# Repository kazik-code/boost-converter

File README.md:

# Przetwornica Boost — README

Autorski projekt przetwornicy podwyższającej napięcie (DC-DC step-up) z regulacją napięcia wyjściowego (CV) i ograniczeniem prądowym (CC). Projekt obejmuje pełny cykl inżynierski: schemat → symulacja LTSpice → projekt PCB (KiCad) → montaż → pomiary i weryfikacja na sprzęcie.

**Projekt grupowy:** 3×Kuba, 1×Szymon

---

## Kluczowe Parametry

| Parametr | Wartość spec. |
| --- | --- |
| Częstotliwość kluczowania | ~1,6 MHz |
| Indukcyjność cewki | L1 = 40 µH |
| Pojemność wyjściowa (bulk) | C2 = 200 µF |
| Próg ograniczenia prądu (CC) | ~300 mA |
| Napięcie wyjściowe (CV) | regulowane przez RV1 |
| Napięcie wejściowe | [Vin] V |

---

## Schemat Blokowy

## Architektura Układu

### 1. Stopień Boost — LM27313XMF + L1 + D1

**LM27313XMF** to kontroler PWM przetwornicy boost o stałej częstotliwości (~1,6 MHz). Reguluje napięcie wyjściowe porównując napięcie na pinie FB z wewnętrznym napięciem referencyjnym — wyższe napięcie FB oznacza większy współczynnik wypełnienia.

Gdy wewnętrzny przełącznik (SW) zamknięty, zwiera dolny koniec cewki **L1 (40 µH)** do masy — prąd narasta, gromadząc energię w polu magnetycznym. Gdy SW otwiera się, pole opada i cewka działa jako źródło prądu napędzające wyjście do napięcia wyższego niż wejście.

**D1 (1N5822 Schottky)** — dioda swobodnego biegu. Gdy SW otwiera się, zapewnia jedyną ścieżkę przepływu prądu cewki. Bez niej zanikające pole wytworzyłoby skok napięcia niszczący U1. Schottky wybrano ze względu na niski spadek napięcia (~0,35 V vs ~0,7 V dla krzemu) i zerowy czas rekombinacji nośników odwrotnych — kluczowe przy 1,574 MHz.

**RV1 (potencjometr 100 kΩ)** ustawia napięcie na pinie FB, regulując tym samym napięcie wyjściowe. **C3 (2,2 µF)** blokuje zakłócenia HF na zasilaniu LM27313.

### 2. Filtr Wyjściowy

| Element | Wartość | Rola |
| --- | --- | --- |
| C1 | 200 pF | Ceramiczny bypass HF — tłumi szumy kluczowania |
| C2 | 200 µF | Elektrolityczny bulk — główny rezerwuar energii, stabilizuje wyjście między cyklami |
| C4 | 10 pF | Drugi bypass HF, blisko wejścia LM317 |

### 3. Pomiar Prądu Cewki — R2 + U2A

**R2 (1 Ω)** w szeregu z torem mocy (bypassowalny przez SW2). Wzmacniacz różnicowy **U2A** (LM358, R3=R4=R5=R6=9,53 kΩ, wzmocnienie = 1) mierzy spadek napięcia:

```
V_out(U2A) = I_cewki × 1 Ω
```

Wynik dostępny na **J3** do zewnętrznego pomiaru. SW2 pozwala ominąć R2 eliminując straty I²R gdy monitoring nie jest potrzebny.

### 4. Regulacja CV/CC — LM317 + U2B + Q1

**LM317 (U3)** jako liniowy regulator po stopniu boost, utrzymuje 1,25 V między OUT i ADJ. **R7** ustawia bazowe napięcie wyjściowe.

**R8 ‖ R9 = 0,5 Ω** mierzą prąd wyjściowy. **U2B** (LM358, wzmacniacz nieodwracający) wzmacnia sygnał:

```
Wzmocnienie = 1 + R11/R10 = 1 + 24k/3,3k ≈ 8,27

Przy I_out = 300 mA:
  V_sense = 0,300 × 0,5  = 0,150 V
  V_U2B   = 0,150 × 8,27 ≈ 1,24 V  ≈  V_ref(LM317) = 1,25 V
```

Gdy V_U2B ≈ 1,25 V, **Q1 (NPN)** przewodzi i ściąga pin ADJ do masy — LM317 obniża napięcie wyjściowe utrzymując I_out ≈ 300 mA (tryb CC). Poniżej progu Q1 zatkany, LM317 reguluje normalnie (tryb CV). Elegancja projektu: próg CC jest wyznaczony przez napięcie referencyjne samego LM317 — bez osobnego komparatora.

---

## Schemat i PCB

### Schemat (KiCad)

### Render 3D PCB

### Zmontowana płytka

Płytka dwuwarstwowa z wyraźną separacją torów mocy i sygnałowych. Toroidalny rdzeń cewki L1, LM317 z radiatorem, kondensatory elektrolityczne i wyjściowe listwy śrubowe.

---

## Symulacja (LTSpice)

### Prąd cewki I(L1) i sygnał kluczujący

---

## Pomiary na Sprzęcie

**Sprzęt:** Rigol MSO5204 (200 MHz, 8 GSa/s)

### Prąd cewki i sygnał kluczujący — pomiar rzeczywisty

**Obserwacja — zniekształcenia pomiaru prądu:**

Pomiar prądu cewki w rzeczywistości wykazuje znaczny szum w porównaniu do symulacji. Przyczyny:

- Sygnał przełączający LM27313 (1,574 MHz) ma bardzo krótkie czasy narastania/opadania generujące harmoniczne rzędu 10–100 MHz
- Pasożytnicza indukcyjność ścieżek PCB i elementów w pętli kluczowania tworzy impulsy napięciowe przy każdym przełączeniu
- Te szybkie transjenty są indukowane (sprzężenie pojemnościowe i indukcyjne) do ścieżki pomiaru prądu
- Efektywna szerokość pasma toru pomiaru (R2 → U2A → J3 → sonda) jest ograniczona, co wypacza kształt sygnału

Wyniku nie należy interpretować jako błędu układu — przetwornica działa poprawnie, co potwierdza pomiar częstotliwości.

### Pomiar częstotliwości kluczowania

> 📎 Wstaw zdjęcie z oscyloskopu — pomiar kursorem (Δx = 635 ns)
> 

| Parametr | Wartość |
| --- | --- |
| Zmierzona częstotliwość | **1,574 MHz** |
| Metoda pomiaru | kursor ΔX: Δx = 635 ns → f = 1/635 ns |
| Specyfikacja LM27313 | ~1,6 MHz (typ.) |
| Odchyłka od specyfikacji | **1,6%** — w granicach tolerancji |

---

## Uwagi do Layoutu PCB

- **Tor mocy (VIN → L1 → D1 → C2 → LM317 → J2):** krótkie i szerokie ścieżki — każda dodatkowa impedancja w tej pętli pogarsza sprawność i zwiększa EMI
- **Kondensatory blokujące (C3, C1, C4):** umieszczone jak najbliżej pinów zasilania układów scalonych
- **Rezystory pomiarowe (R2, R8, R9):** połączenia Kelvin (oddzielne ścieżki prądu i pomiaru) eliminują błąd od rezystancji ścieżki
- **Masa:** ciągłe wypełnienie miedzią z separacją głośnego prądu kluczowania od cichego toru analogowego (LM358, dzielnik FB)
- **Punkty testowe:** VIN, węzeł SW (U1 pin 1), wyjście L1/anoda D1, VOUT, J3 (monitor cewki)

---

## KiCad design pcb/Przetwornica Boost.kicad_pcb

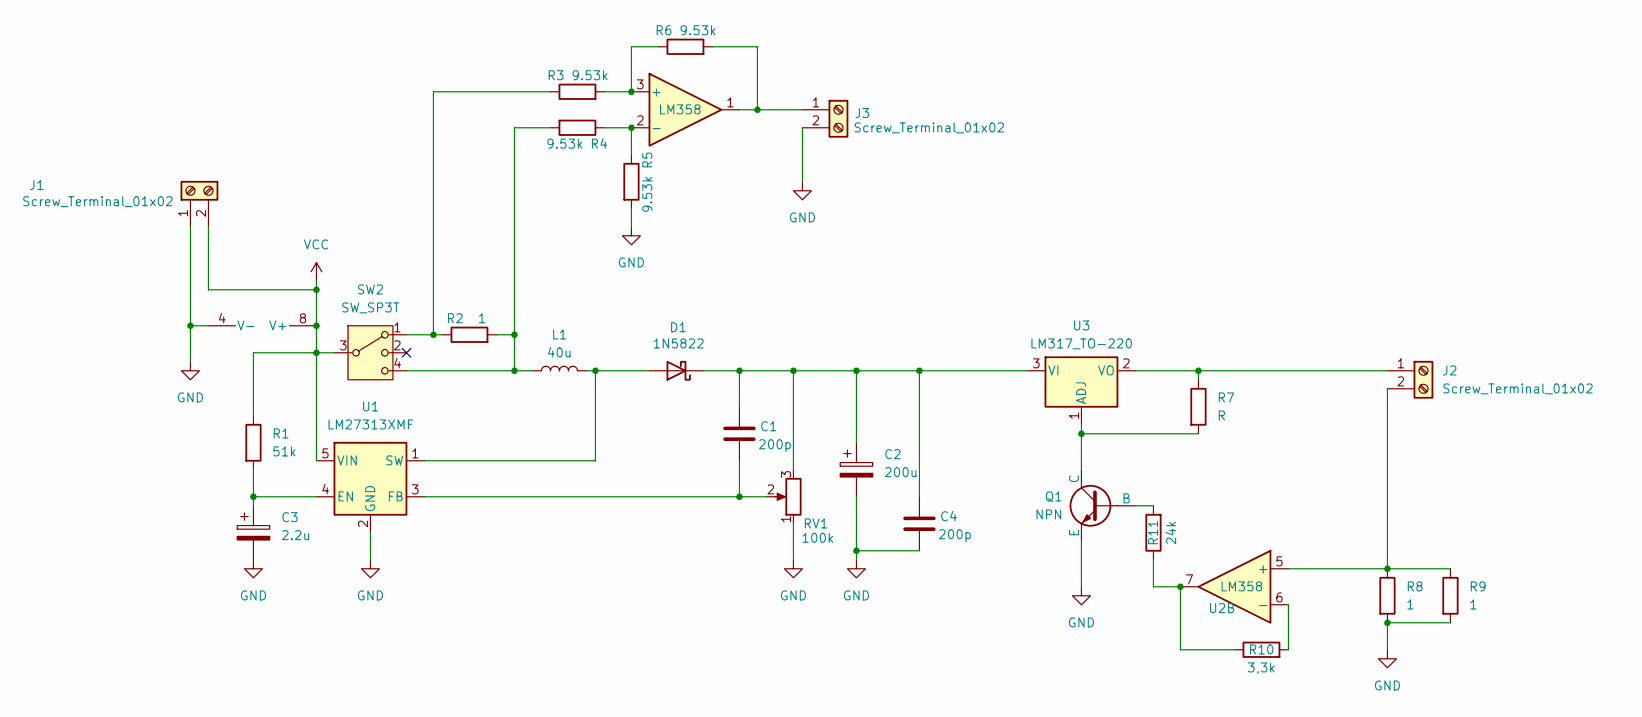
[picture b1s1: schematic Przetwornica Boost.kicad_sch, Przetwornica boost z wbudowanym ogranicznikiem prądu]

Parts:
C1, C4: 200p; C_Disc_D4.3mm_W1.9mm_P5.00mm
C2: 200u; CP_Elec_10x10.5
C3: 2.2u; CP_Radial_D5.0mm_P2.50mm
D1: 1N5822; D_DO-201_P12.70mm_Horizontal
J1, J2, J3: Screw_Terminal_01x02; TerminalBlock_MaiXu_MX126-5.0-02P_1x02_P5.00mm
L1: 40u; Inductor L1
Q1: NPN; TO-92_Inline
R1: 51k; R_Axial_DIN0204_L3.6mm_D1.6mm_P7.62mm_Horizontal
R2, R8, R9: 1; R_Axial_DIN0309_L9.0mm_D3.2mm_P12.70mm_Horizontal
R3, R4, R5, R6: 9.53k; R_Axial_DIN0204_L3.6mm_D1.6mm_P7.62mm_Horizontal
R7: R; R_Axial_DIN0204_L3.6mm_D1.6mm_P7.62mm_Horizontal
R10: 3,3k; R_Axial_DIN0204_L3.6mm_D1.6mm_P7.62mm_Horizontal
R11: 24k; R_Axial_DIN0204_L3.6mm_D1.6mm_P7.62mm_Horizontal
RV1: 100k; Potentiometer_Bourns_3296W_Vertical
SW2: SW_SP3T; Switch
U1: LM27313XMF; SOT-23-5
U2: LM358; DIP-8_W7.62mm
U3: LM317_TO-220; TO-220-3_Vertical

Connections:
GND: C2.2, C3.2, C4.2, J1.1, J3.2, Q1.3 (E), R5.2, R8.2, R9.2, RV1.1, U1.2 (GND), U2.4 (V-)
unnamed: D1.2 (A), L1.2, U1.1 (SW)
unnamed: C1.1, C2.1, C4.1, D1.1 (K), RV1.3, U3.3 (VI)
unnamed: J2.1, R7.1, U3.2 (VO)
unnamed: J2.2, R8.1, R9.1, U2.5 (+)
unnamed: J3.1, R6.2, U2.1
unnamed: L1.1, R2.2, R4.2, SW2.4
unnamed: Q1.2 (B), R11.2
unnamed: Q1.1 (C), R7.2, U3.1 (ADJ)
unnamed: R2.1, R3.1, SW2.1
unnamed: R10.1, R11.1, U2.7
unnamed: C3.1, R1.2, U1.4 (EN)
unnamed: C1.2, RV1.2, U1.3 (FB)
unnamed: R3.2, R6.1, U2.3 (+)
unnamed: R4.1, R5.1, U2.2 (-)
unnamed: R10.2, U2.6 (-)
VCC: J1.2, R1.1, SW2.3, U1.5 (VIN), U2.8 (V+)

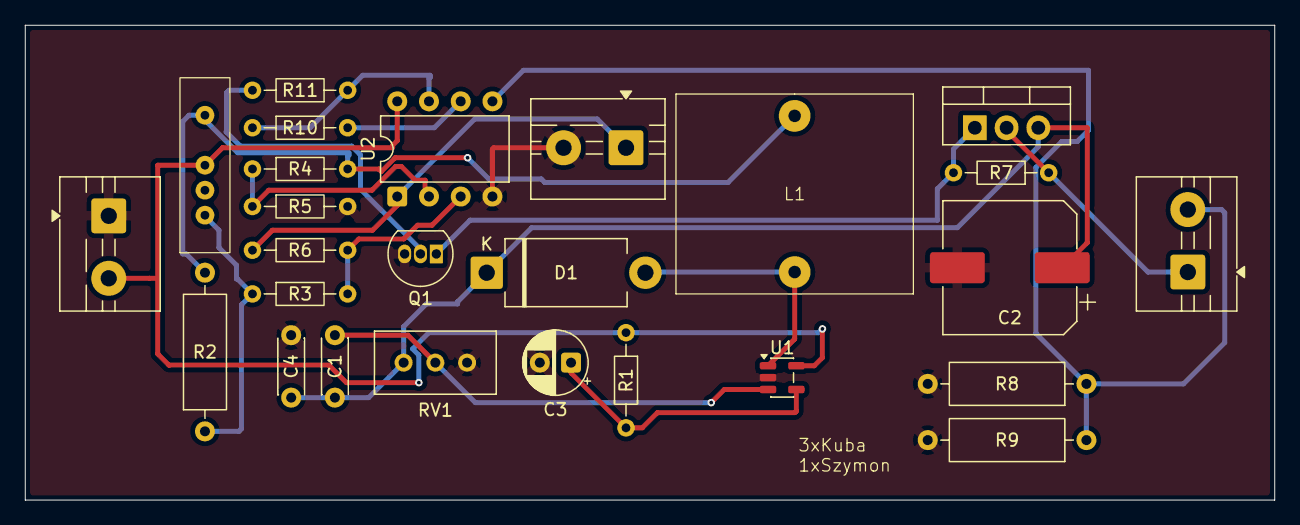
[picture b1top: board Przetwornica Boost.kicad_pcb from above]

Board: 4 copper layers, 100.0 x 38.0 mm, 26 parts (0 on the bottom side), 17 nets.

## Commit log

2026-05-27 Add LTSpice simulation
2026-05-27 Initial commit — boost converter hardware project KiCad schematic and PCB, gerbers, custom footprints, docs with images.
